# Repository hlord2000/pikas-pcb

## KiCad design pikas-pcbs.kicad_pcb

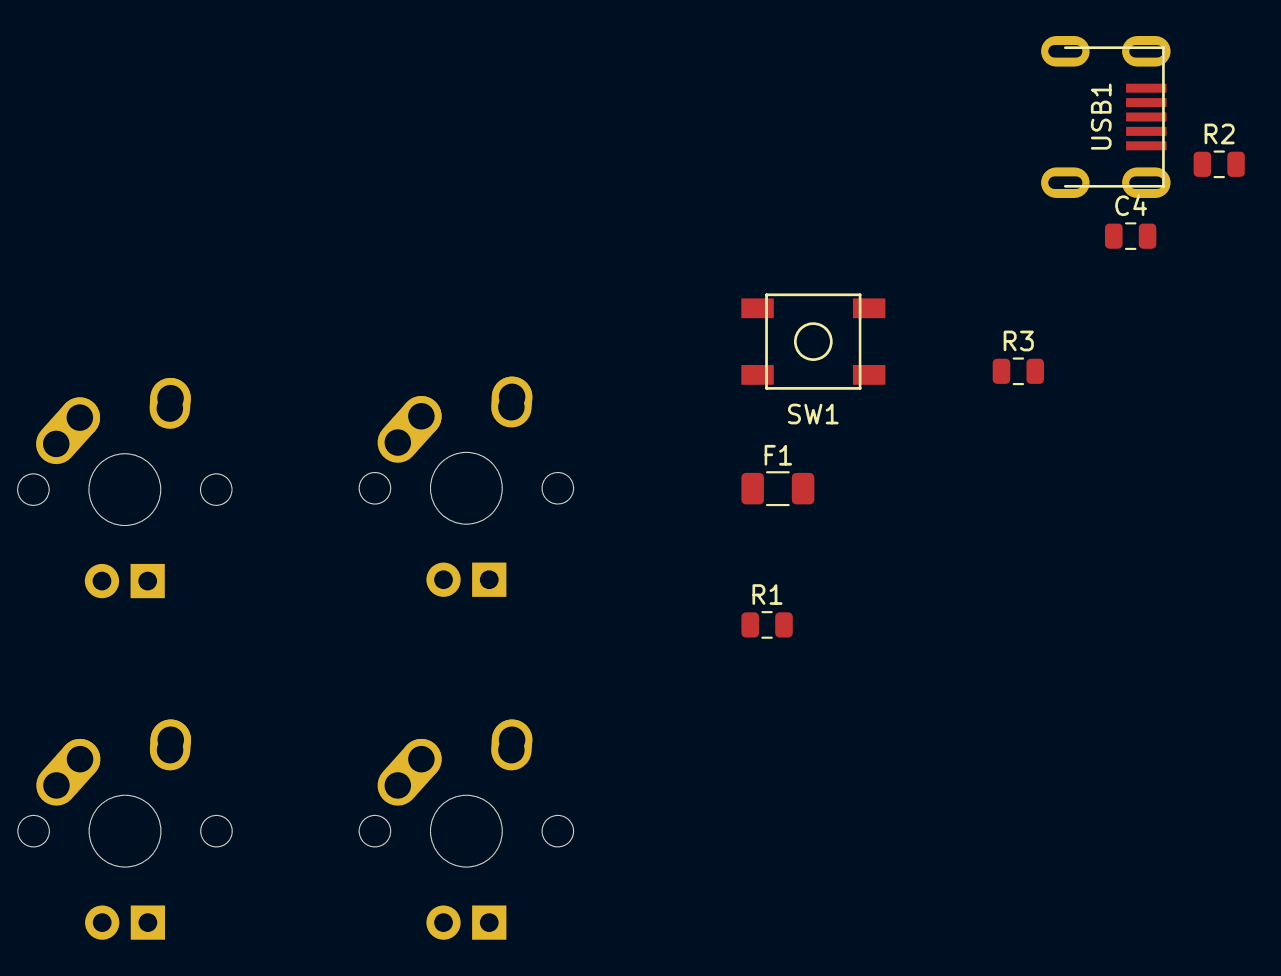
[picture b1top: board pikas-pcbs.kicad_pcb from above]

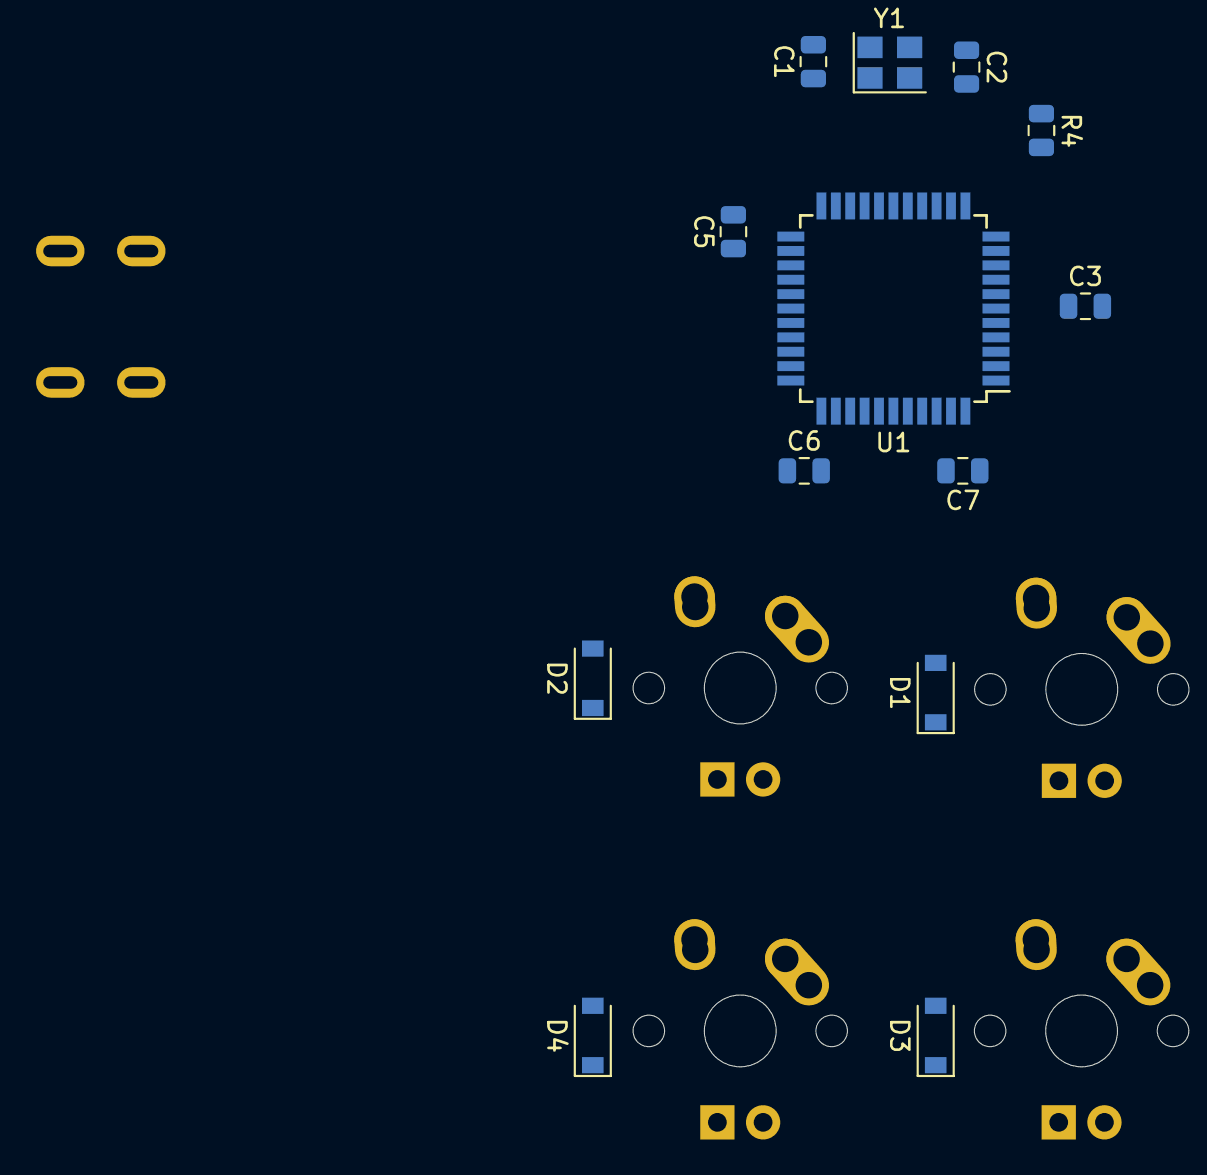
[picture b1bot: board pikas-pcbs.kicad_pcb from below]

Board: 2 copper layers, 24 parts (13 on the bottom side), 20 nets, no tracks yet.

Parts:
C1, C2: 0.1uF; C_0805_2012Metric
C3, C4: 22pF; C_0805_2012Metric
C5: 0.1uf; C_0805_2012Metric
C6: 1uF; C_0805_2012Metric
C7: 10uF; C_0805_2012Metric
D1, D2, D3, D4: D_Small; D_SOD-123
F1: Polyfuse; Fuse_1206_3216Metric
MX1, MX2, MX3, MX4: MX-NoLED; MX-1U
R1, R2: 22; R_0805_2012Metric
R3: R_Small; R_0805_2012Metric
R4: 10k; R_0805_2012Metric
SW1: SW_Push; SKQG-1155865
U1: ATmega32U4-AU; TQFP-44_10x10mm_P0.8mm
USB1: Molex-0548190589
Y1: 16MHz; Crystal_SMD_3225-4Pin_3.2x2.5mm

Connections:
+5V: C1.1, C2.1, C5.1, C7.1, F1.1, R3.1, U1.2, U1.7, U1.14, U1.24, U1.34, U1.44
D+: R2.1, USB1.3
D-: R1.1, USB1.4
GND: C1.2, C2.2, C3.2, C4.2, C5.2, C6.2, C7.2, R4.1, SW1.1, U1.5, U1.15, U1.23, U1.35, U1.43, USB1.1, Y1.2, Y1.4
unnamed: C3.1, U1.17, Y1.1
unnamed: C4.1, U1.16, Y1.3
unnamed: C6.1, U1.6
unnamed: D1.2, MX1.2
unnamed: D2.2, MX2.2
unnamed: D3.2, MX3.2
unnamed: D4.2, MX4.2
unnamed: MX1.1, MX2.1
unnamed: MX3.1, MX4.1
unnamed: R1.2, U1.3
unnamed: R2.2, U1.4
unnamed: R3.2, SW1.2, U1.13
unnamed: R4.2, U1.33
ROW0: D1.1, D3.1
ROW1: D2.1, D4.1
VCC: F1.2, USB1.5

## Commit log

2023-04-09 Add submodules
2023-04-09 Add Sym/foot LIBS
2023-04-09 Pcb!
2023-04-09 PCB Update
2023-04-09 save checkpoint
2023-04-09 check2
2023-04-10 Forgotten check
2023-04-11 Create _autosave-pikas-pcbs.kicad_pcb
    ROUNDED CORNERS AND (hopefully dont foreshadow jinx) FINISHED BOARD
2023-04-11 adjusted
2023-04-11 Adjusted schematic
